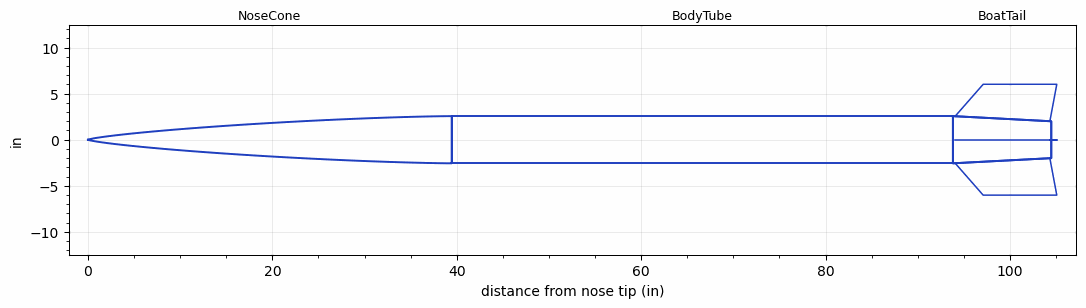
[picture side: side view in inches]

<RASAeroDocument>
 <FileVersion>2</FileVersion>
 <RocketDesign>
  <NoseCone>
   <Length>39.44882</Length>
   <Diameter>5.11811</Diameter>
   <Shape>Von Karman Ogive</Shape>
   <Location>0</Location>
  </NoseCone>
  <BodyTube>
   <Length>54.37</Length>
   <Diameter>5.11811</Diameter>
   <Location>39.44882</Location>
   <BoattailLength>10.6693</BoattailLength>
   <BoattailRearDiameter>4</BoattailRearDiameter>
  </BodyTube>
  <BoatTail>
   <Length>10.6693</Length>
   <Diameter>5.11811</Diameter>
   <RearDiameter>4</RearDiameter>
   <Location>93.81882</Location>
   <Fin>
    <Count>4</Count>
    <Chord>10.2737</Chord>
    <Span>3.4646</Span>
    <SweepDistance>3.037</SweepDistance>
    <TipChord>7.9866</TipChord>
    <Thickness>0.2362</Thickness>
    <LERadius>0.0197</LERadius>
    <Location>10.4252</Location>
    <AirfoilSection>Double Wedge</AirfoilSection>
    <FX1>3</FX1>
   </Fin>
  </BoatTail>
  <Surface>Camouflage Paint</Surface>
  <ModifiedBarrowman>True</ModifiedBarrowman>
  <Turbulence>False</Turbulence>
  <SustainerNozzle>2.97</SustainerNozzle>
  <UseBooster1>False</UseBooster1>
  <UseBooster2>False</UseBooster2>
 </RocketDesign>
 <LaunchSite>
  <Altitude>0</Altitude>
  <Pressure>29.53</Pressure>
  <RodAngle>0</RodAngle>
  <RodLength>13.12</RodLength>
  <Temperature>41</Temperature>
  <WindSpeed>0</WindSpeed>
 </LaunchSite>
 <Recovery>
  <Altitude1>1000</Altitude1>
  <Altitude2>1000</Altitude2>
  <DeviceType1>Parachute</DeviceType1>
  <DeviceType2>Parachute</DeviceType2>
  <Event1>True</Event1>
  <Event2>True</Event2>
  <Size1>36</Size1>
  <Size2>72</Size2>
  <EventType1>Apogee</EventType1>
  <EventType2>Altitude</EventType2>
  <CD1>0.97</CD1>
  <CD2>2.2</CD2>
 </Recovery>
 <MachAlt>
  <Item>2, 1000</Item>
  <Item>0, 0</Item>
  <Item>2, 100000</Item>
  <Item>2, 1000</Item>
  <Item>0, 0</Item>
  <Item>2, 100000</Item>
 </MachAlt>
 <SimulationList>
  <Simulation>
   <SustainerEngine>O3400-IM-P  (CTI)</SustainerEngine>
   <SustainerLaunchWt>53.01</SustainerLaunchWt>
   <SustainerNozzleDiameter>2.7</SustainerNozzleDiameter>
   <SustainerCG>68.69</SustainerCG>
   <SustainerIgnitionDelay>0</SustainerIgnitionDelay>
   <Booster1SeparationDelay>0</Booster1SeparationDelay>
   <Booster1IgnitionDelay>0</Booster1IgnitionDelay>
   <IncludeBooster1>False</IncludeBooster1>
   <Booster2Delay>0</Booster2Delay>
   <IncludeBooster2>False</IncludeBooster2>
   <TimetoApogee>49.19775</TimetoApogee>
   <MaxAltitude>50356.38</MaxAltitude>
   <MaxVelocity>2958.433</MaxVelocity>
  </Simulation>
  <Simulation>
   <SustainerEngine>K2050  (AT)</SustainerEngine>
   <SustainerLaunchWt>20.94</SustainerLaunchWt>
   <SustainerNozzleDiameter>2</SustainerNozzleDiameter>
   <SustainerCG>64.15</SustainerCG>
   <SustainerIgnitionDelay>0</SustainerIgnitionDelay>
   <Booster1SeparationDelay>0</Booster1SeparationDelay>
   <Booster1IgnitionDelay>0</Booster1IgnitionDelay>
   <IncludeBooster1>False</IncludeBooster1>
   <Booster2Delay>0</Booster2Delay>
   <IncludeBooster2>False</IncludeBooster2>
   <TimetoApogee>13.26021</TimetoApogee>
   <MaxAltitude>2910.977</MaxAltitude>
   <MaxVelocity>471.947</MaxVelocity>
  </Simulation>
 </SimulationList>
</RASAeroDocument>
